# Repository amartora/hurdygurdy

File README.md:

A project to create an electric version of a hurdy gurdy, where the crank also generates electricity to power it.

TOTAL WORK IN PROGRESS AS OF NOW

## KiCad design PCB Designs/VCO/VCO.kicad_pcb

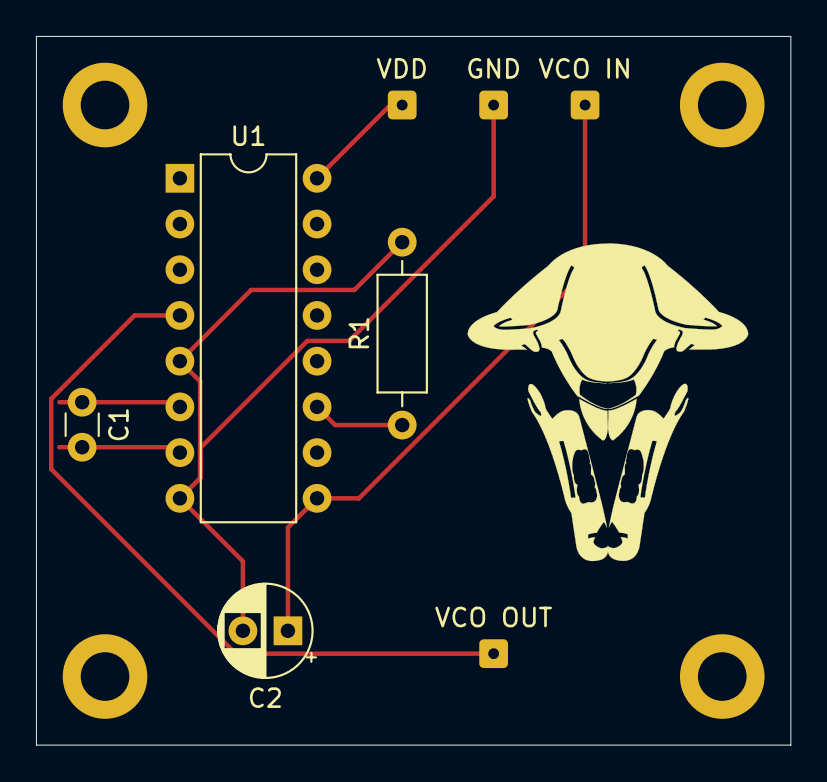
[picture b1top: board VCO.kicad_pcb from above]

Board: 2 copper layers, 41.9 x 39.4 mm, 8 parts (0 on the bottom side), 7 nets.

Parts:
C1: C; C_Disc_D3.0mm_W1.6mm_P2.50mm
C2: CP1; CP_Radial_D5.0mm_P2.50mm
GND: MountingHole_Pad; SolderWire-0.1sqmm_1x01_D0.4mm_OD1mm
R1: R_US; R_Axial_DIN0207_L6.3mm_D2.5mm_P10.16mm_Horizontal
U1: 4046; DIP-16_W7.62mm
VCO IN: MountingHole_Pad; SolderWire-0.1sqmm_1x01_D0.4mm_OD1mm
VCO OUT: MountingHole_Pad; SolderWire-0.1sqmm_1x01_D0.4mm_OD1mm
VDD: MountingHole_Pad; SolderWire-0.1sqmm_1x01_D0.4mm_OD1mm

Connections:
Earth: C2.2, GND.1, R1.2, U1.5, U1.8
unnamed: C1.1, U1.6
unnamed: C1.2, U1.7
unnamed: C2.1, U1.9, VCO IN.1
unnamed: R1.1, U1.11
unnamed: U1.4, VCO OUT.1
unnamed: U1.16, VDD.1

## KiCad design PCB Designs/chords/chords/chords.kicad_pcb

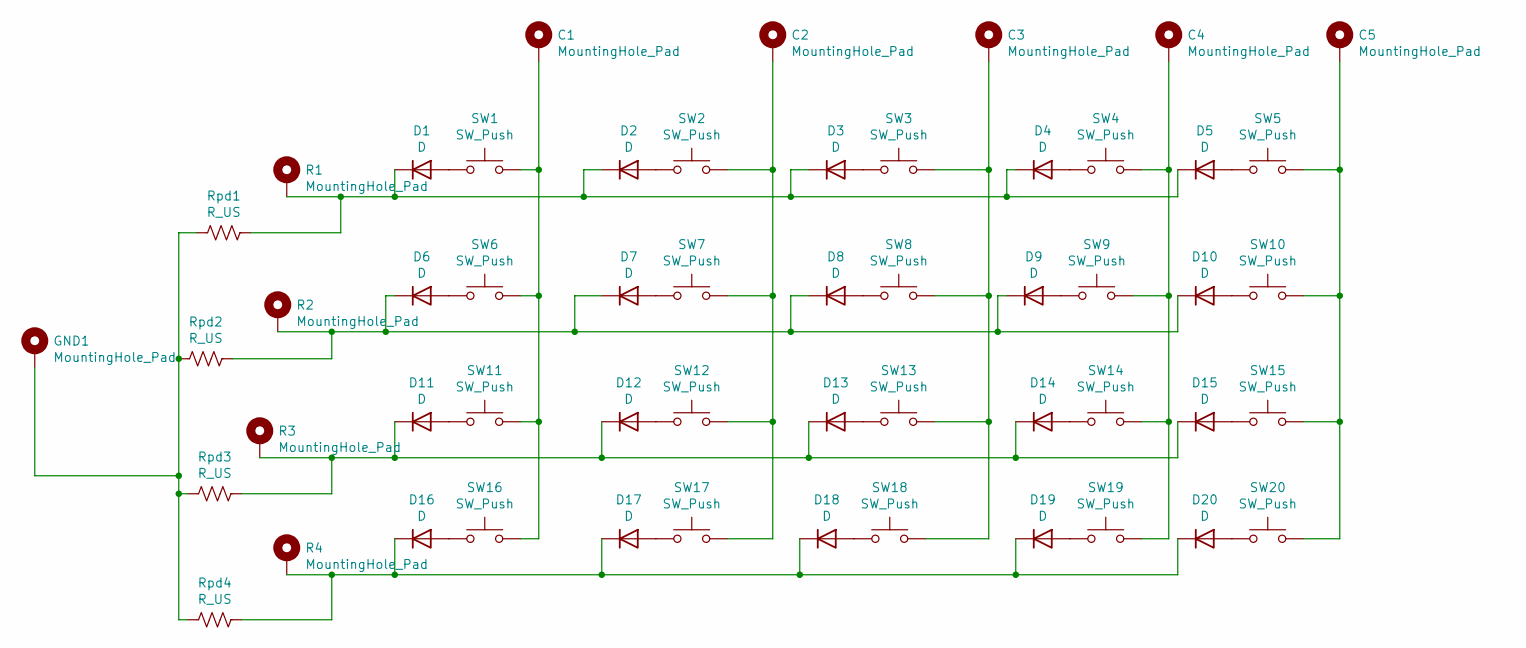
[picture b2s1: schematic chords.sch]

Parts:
C1, C2, C3, C4, C5: MountingHole_Pad; SolderWire-0.1sqmm_1x01_D0.4mm_OD1mm
D1, D2, D3, D4, D5, D6, D7, D8, D9, D10, D11, D12, D13, D14, D15, D16, D17, D18, D19, D20: D; D_SOD-323
GND1: MountingHole_Pad; SolderWire-0.1sqmm_1x01_D0.4mm_OD1mm
R1, R2, R3, R4: MountingHole_Pad; SolderWire-0.1sqmm_1x01_D0.4mm_OD1mm
Rpd1, Rpd2, Rpd3, Rpd4: R_US; R_Axial_DIN0207_L6.3mm_D2.5mm_P10.16mm_Horizontal
SW1, SW2, SW3, SW4, SW5, SW6, SW7, SW8, SW9, SW10, SW11, SW12, SW13, SW14, SW15, SW16, SW17, SW18, SW19, SW20: SW_Push; my switch

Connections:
unnamed: C1.1, SW1.2, SW6.2, SW11.2, SW16.2
unnamed: C2.1, SW2.2, SW7.2, SW12.2, SW17.2
unnamed: C3.1, SW3.2, SW8.2, SW13.2, SW18.2
unnamed: C4.1, SW4.2, SW9.2, SW14.2, SW19.2
unnamed: C5.1, SW5.2, SW10.2, SW15.2, SW20.2
unnamed: D1.1 (K), D2.1 (K), D3.1 (K), D4.1 (K), D5.1 (K), R1.1, Rpd1.2
unnamed: D1.2 (A), SW1.1
unnamed: D2.2 (A), SW2.1
unnamed: D3.2 (A), SW3.1
unnamed: D4.2 (A), SW4.1
unnamed: D5.2 (A), SW5.1
unnamed: D6.2 (A), SW6.1
unnamed: D7.2 (A), SW7.1
unnamed: D8.2 (A), SW8.1
unnamed: D9.2 (A), SW9.1
unnamed: D6.1 (K), D7.1 (K), D8.1 (K), D9.1 (K), D10.1 (K), R2.1, Rpd2.2
unnamed: D10.2 (A), SW10.1
unnamed: D11.1 (K), D12.1 (K), D13.1 (K), D14.1 (K), D15.1 (K), R3.1, Rpd3.2
unnamed: D11.2 (A), SW11.1
unnamed: D12.2 (A), SW12.1
unnamed: D13.2 (A), SW13.1
unnamed: D14.2 (A), SW14.1
unnamed: D15.2 (A), SW15.1
unnamed: D16.1 (K), D17.1 (K), D18.1 (K), D19.1 (K), D20.1 (K), R4.1, Rpd4.2
unnamed: D16.2 (A), SW16.1
unnamed: D17.2 (A), SW17.1
unnamed: D18.2 (A), SW18.1
unnamed: D19.2 (A), SW19.1
unnamed: D20.2 (A), SW20.1
unnamed: GND1.1, Rpd1.1, Rpd2.1, Rpd3.1, Rpd4.1

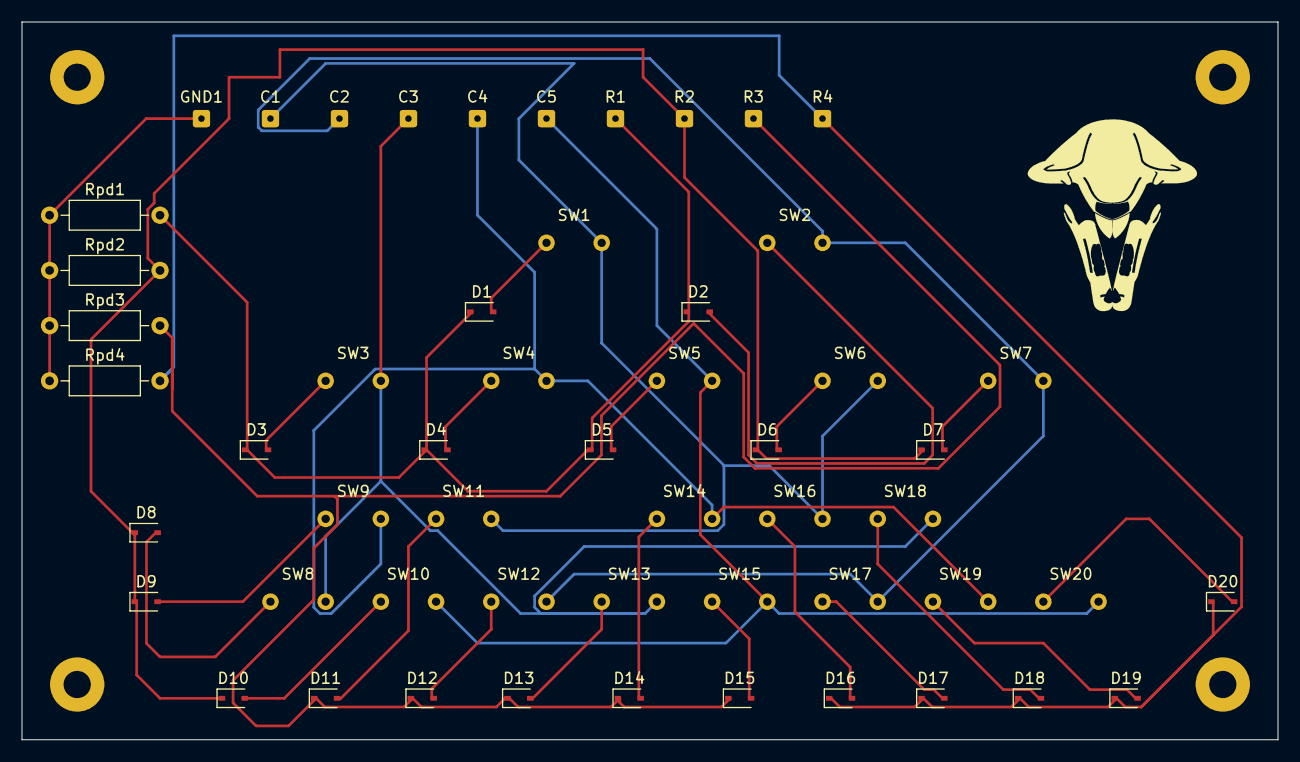
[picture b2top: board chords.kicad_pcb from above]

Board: 2 copper layers, 115.6 x 66.0 mm, 54 parts (0 on the bottom side), 30 nets.

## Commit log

2021-03-30 initial upload for standalone repo
2021-04-04 initial upload
2026-02-24 Added note frequency header file
